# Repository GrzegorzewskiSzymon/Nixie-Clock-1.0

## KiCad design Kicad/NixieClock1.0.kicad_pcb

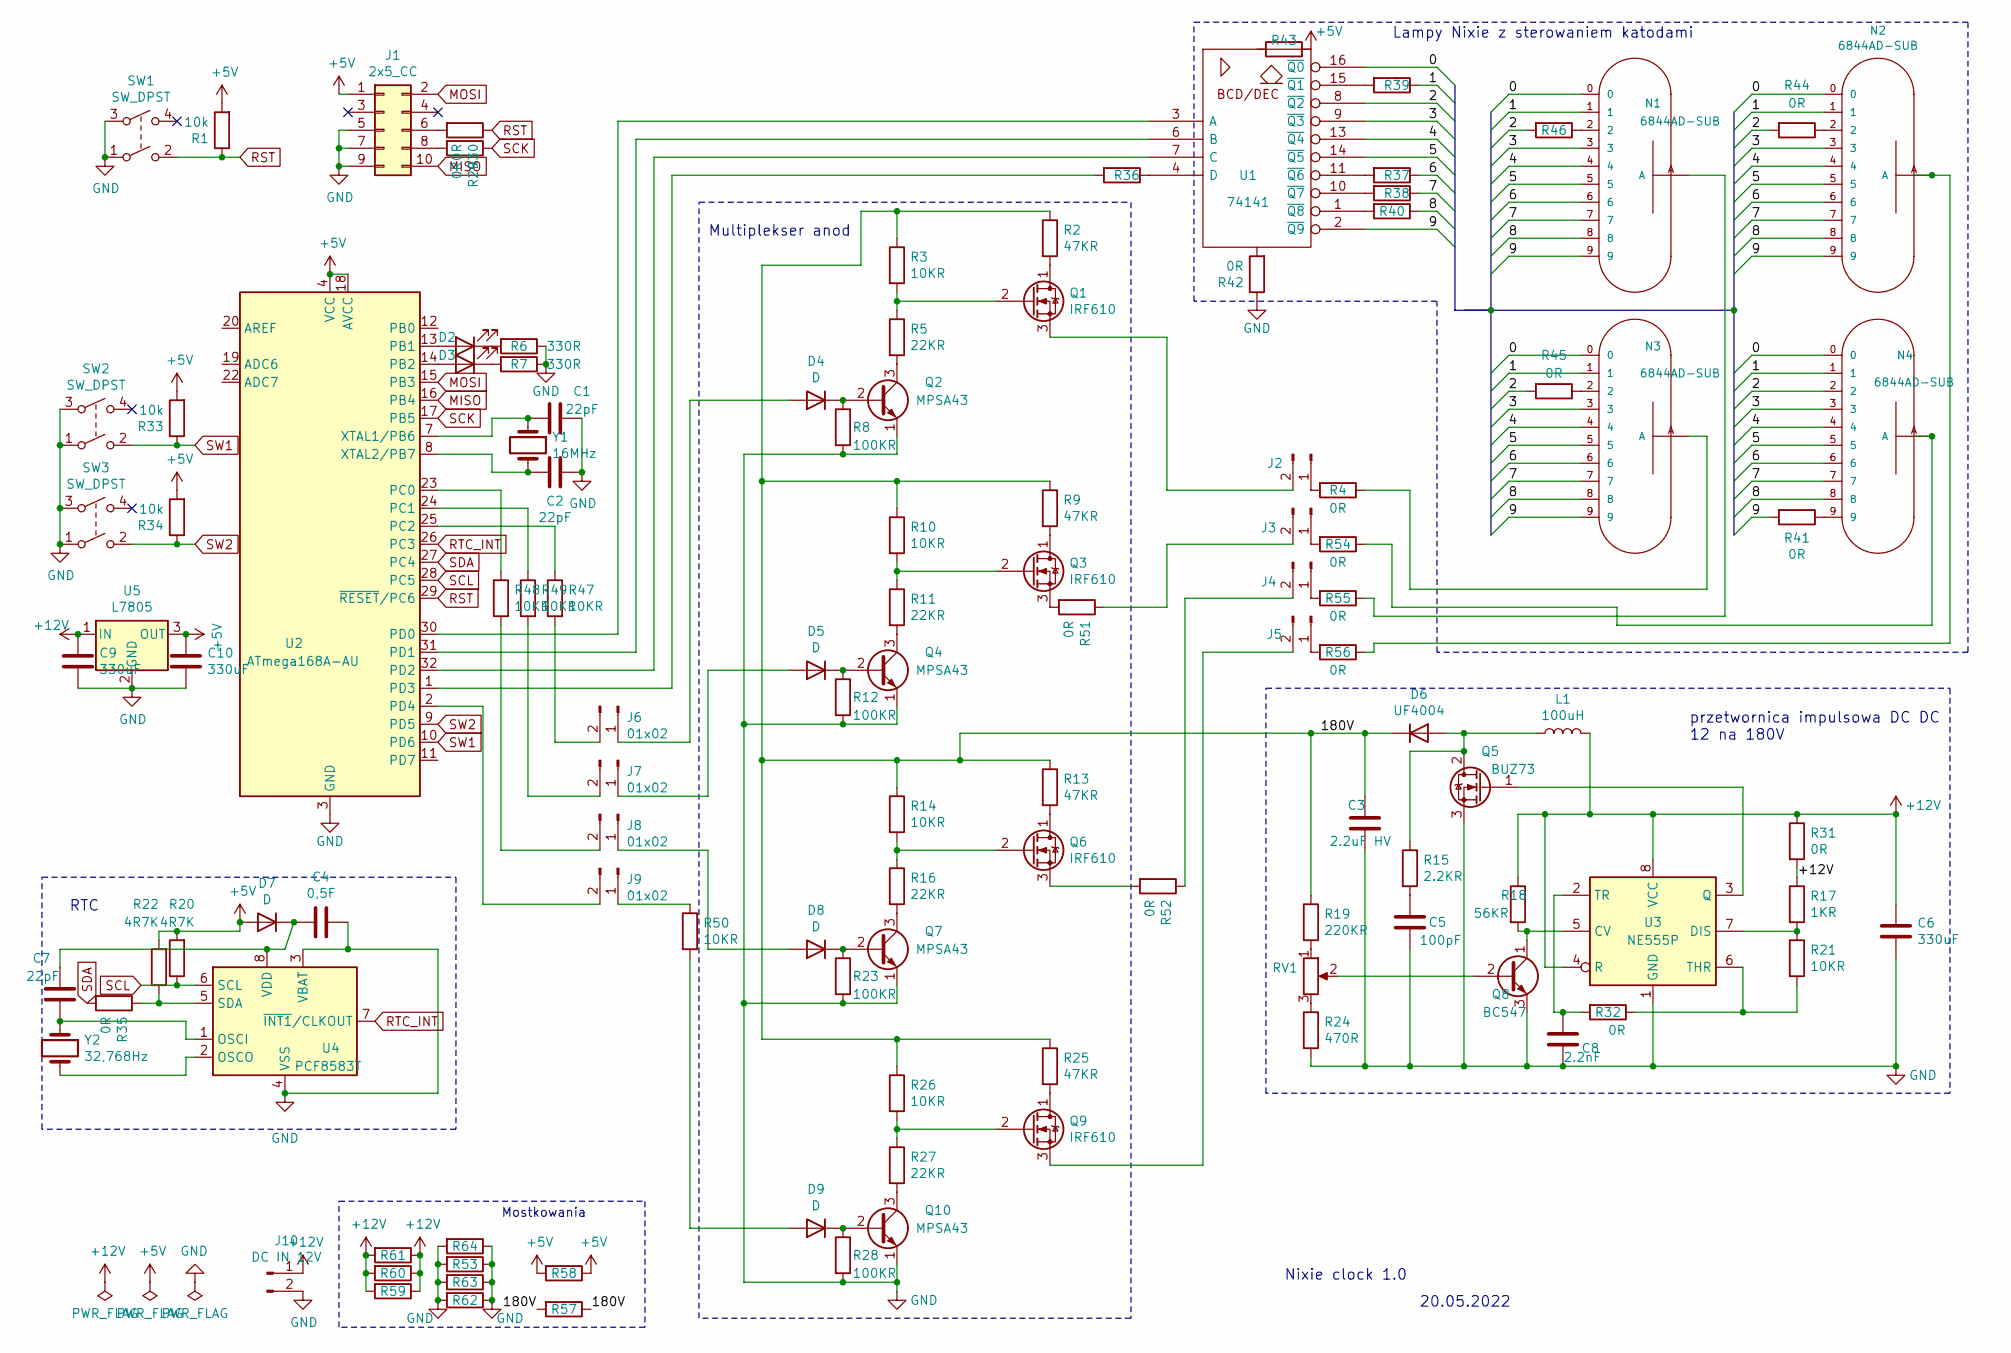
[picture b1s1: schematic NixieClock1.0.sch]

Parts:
C1, C2, C7: 22pF; C_Disc_D3.0mm_W2.0mm_P2.50mm
C3: 2.2uF HV; CP_Radial_D5.0mm_P2.50mm
C4: 0,5F; CP_Radial_D6.3mm_P2.50mm
C5: 100pF; C_Disc_D5.0mm_W2.5mm_P5.00mm
C6, C9, C10: 330uF; CP_Radial_D5.0mm_P2.50mm
C8: 2.2nF; C_Disc_D3.0mm_W2.0mm_P2.50mm
D2, D3: LED; LED_1206_3216Metric_Pad1.42x1.75mm_HandSolder
D4, D5, D7, D8, D9: D; D_DO-34_SOD68_P7.62mm_Horizontal
D6: UF4004; D_DO-34_SOD68_P7.62mm_Horizontal
J1: 2x5_CC; PinSocket_2x05_P2.54mm_Vertical
J2, J3, J4, J5, J6, J7, J8, J9: 01x02; PinHeader_1x02_P2.54mm_Vertical
J10: DC IN 12V; BarrelJack_CUI_PJ-102AH_Horizontal
L1: 100uH; L_Axial_L6.6mm_D2.7mm_P2.54mm_Vertical_Vishay_IM-2
N1, N2, N3, N4: 6844AD-SUB; Z5740m
Q1, Q3, Q6, Q9: IRF610; TO-220-3_Vertical
Q2, Q4, Q7, Q10: MPSA43; TO-92_Inline
Q5: BUZ73; TO-220-3_Vertical
Q8: BC547; TO-92_Inline
R1, R33, R34: 10k; R_1206_3216Metric_Pad1.30x1.75mm_HandSolder
R2, R9, R13, R25: 47KR; R_Axial_DIN0207_L6.3mm_D2.5mm_P7.62mm_Horizontal
R3, R10, R14, R21, R26, R50: 10KR; R_1206_3216Metric_Pad1.30x1.75mm_HandSolder
R4, R30, R31, R32, R36, R37, R38, R42, R43, R54, R55, R56, R57, R58, R59, R64: 0R; R_Axial_DIN0207_L6.3mm_D2.5mm_P7.62mm_Horizontal
R5, R11, R16, R27: 22KR; R_Axial_DIN0207_L6.3mm_D2.5mm_P7.62mm_Horizontal
R6, R7: 330R; R_1206_3216Metric_Pad1.30x1.75mm_HandSolder
R8, R12, R23, R28: 100KR; R_Axial_DIN0207_L6.3mm_D2.5mm_P7.62mm_Horizontal
R15: 2.2KR; R_Axial_DIN0207_L6.3mm_D2.5mm_P7.62mm_Horizontal
R17: 1KR; R_Axial_DIN0207_L6.3mm_D2.5mm_P7.62mm_Horizontal
R18: 56KR; R_Axial_DIN0207_L6.3mm_D2.5mm_P7.62mm_Horizontal
R19: 220KR; R_Axial_DIN0207_L6.3mm_D2.5mm_P7.62mm_Horizontal
R20, R22: 4R7K; R_Axial_DIN0207_L6.3mm_D2.5mm_P7.62mm_Horizontal
R24: 470R; R_Axial_DIN0207_L6.3mm_D2.5mm_P7.62mm_Horizontal
R29, R35, R40, R41, R44, R45, R46, R51, R52, R53, R60, R61, R62, R63: 0R; R_1206_3216Metric_Pad1.30x1.75mm_HandSolder
R39: e; R_1206_3216Metric_Pad1.30x1.75mm_HandSolder
R47, R48, R49: 10KR; R_Axial_DIN0207_L6.3mm_D2.5mm_P7.62mm_Horizontal
RV1: R_POT 1K; Potentiometer_ACP_CA9-H2,5_Horizontal
SW1, SW2, SW3: SW_DPST; SW_PUSH_6mm_H4.3mm
U1: 74141; DIP-16_W7.62mm_Socket_LongPads
U2: ATmega168A-AU; TQFP-32_7x7mm_P0.8mm
U3: NE555P; DIP-8_W7.62mm
U4: PCF8583T; SOIC-8_3.9x4.9mm_P1.27mm
U5: L7805; DPAK-3
Y1: 16MHz; Resonator-2Pin_W10.0mm_H5.0mm
Y2: 32,768Hz; Crystal_DS15_D1.5mm_L5.0mm_Vertical

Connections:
+5V: C10.1, D7.2 (A), J1.1, R1.2, R20.2, R22.2, R33.2, R34.2, R43.2, R58.1, R58.2, U2.4 (VCC), U2.6 (VCC), U2.18 (AVCC), U5.3 (OUT)
+12V: C6.1, C9.1, J10.1, L1.2, R17.1, R18.1, R31.1, R31.2, R59.1, R59.2, R60.1, R60.2, R61.1, R61.2, U3.4 (R), U3.8 (VCC), U5.1 (IN)
/0: N1.0, N2.0, N3.0, N4.0, U1.16 (~Q0)
/1: N1.1, N2.1, N3.1, N4.1, R39.1
/2: N4.2, R44.2, R45.2, R46.2, U1.8 (~Q2)
/3: N1.3, N2.3, N3.3, N4.3, U1.9 (~Q3)
/4: N1.4, N2.4, N3.4, N4.4, U1.13 (~Q4)
/5: N1.5, N2.5, N3.5, N4.5, U1.14 (~Q5)
/6: N1.6, N2.6, N3.6, N4.6, R37.1
/7: N1.7, N2.7, N3.7, N4.7, R38.1
/8: N1.8, N2.8, N3.8, N4.8, R40.1
/9: N1.9, N2.9, N3.9, R41.2, U1.2 (~Q9)
/180V: C3.1, D6.1 (K), R2.1, R3.1, R9.1, R10.1, R13.1, R14.1, R19.1, R25.1, R26.1, R57.1, R57.2
MISO: J1.10, U2.16 (PB4)
MOSI: J1.2, U2.15 (PB3)
unnamed: C1.2, U2.7 (XTAL1/PB6), Y1.1
unnamed: C2.2, U2.8 (XTAL2/PB7), Y1.2
unnamed: C5.1, R15.2
unnamed: C7.1, U4.1 (OSCI), Y2.1
unnamed: C8.1, R32.2, U3.2 (TR)
unnamed: D2.1 (K), R6.2
unnamed: D2.2 (A), U2.13 (PB1)
unnamed: D3.1 (K), R7.2
unnamed: D3.2 (A), U2.14 (PB2)
unnamed: D4.1 (K), Q2.2 (B), R8.1
unnamed: D4.2 (A), J6.1
unnamed: D5.1 (K), Q4.2 (B), R12.1
unnamed: D5.2 (A), J7.1
unnamed: D6.2 (A), L1.1, Q5.2 (D), R15.1
unnamed: D8.1 (K), Q7.2 (B), R23.1
unnamed: D8.2 (A), J8.1
unnamed: D9.1 (K), Q10.2 (B), R28.1
unnamed: D9.2 (A), R50.2
unnamed: J1.6, R30.2
unnamed: J1.8, R29.2
unnamed: J2.1, R4.2
unnamed: J2.2, Q1.3 (S)
unnamed: J3.1, R54.2
unnamed: J3.2, R51.1
unnamed: J4.1, R55.2
unnamed: J4.2, R52.1
unnamed: J5.1, R56.2
unnamed: J5.2, Q9.3 (S)
unnamed: J6.2, R47.2
unnamed: J7.2, R49.2
unnamed: J8.2, R48.2
unnamed: J9.1, R50.1
unnamed: J9.2, U2.2 (PD4)
unnamed: N1.2, R46.1
unnamed: N1.A, R55.1
unnamed: N2.2, R44.1
unnamed: N2.A, R56.1
unnamed: N3.2, R45.1
unnamed: N3.A, R4.1
unnamed: N4.9, R41.1
unnamed: N4.A, R54.1
unnamed: Q1.1 (D), R2.2
unnamed: Q1.2 (G), R3.2, R5.1
unnamed: Q2.3 (C), R5.2
unnamed: Q3.1 (D), R9.2
unnamed: Q3.2 (G), R10.2, R11.1
unnamed: Q3.3 (S), R51.2
unnamed: Q4.3 (C), R11.2
unnamed: Q5.1 (G), U3.3 (Q)
unnamed: Q6.1 (D), R13.2
unnamed: Q6.2 (G), R14.2, R16.1
unnamed: Q6.3 (S), R52.2
unnamed: Q7.3 (C), R16.2
unnamed: Q8.1 (C), R18.2, U3.5 (CV)
unnamed: Q8.2 (B), RV1.2
unnamed: Q9.1 (D), R25.2
unnamed: Q9.2 (G), R26.2, R27.1
unnamed: Q10.3 (C), R27.2
unnamed: R17.2, R21.1, U3.7 (DIS)
unnamed: R19.2, RV1.1
unnamed: R21.2, R32.1, U3.6 (THR)
unnamed: R22.1, R35.1, U4.5 (SDA)
unnamed: R24.1, RV1.3
unnamed: R36.1, U1.4 (D)
unnamed: R36.2, U2.1 (PD3)
unnamed: R37.2, U1.11 (~Q6)
unnamed: R38.2, U1.10 (~Q7)
unnamed: R39.2, U1.15 (~Q1)
unnamed: R40.2, U1.1 (~Q8)
unnamed: R47.1, U2.25 (PC2)
unnamed: R48.1, U2.23 (PC0)
unnamed: R49.1, U2.24 (PC1)
unnamed: U1.3 (A), U2.30 (PD0)
unnamed: U1.6 (B), U2.31 (PD1)
unnamed: U1.7 (C), U2.32 (PD2)
unnamed: U4.2 (OSCO), Y2.2
RST: R1.1, R30.1, SW1.2, U2.29 (~RESET~/PC6)
RTC_INT: U2.26 (PC3), U4.7 (~INT1~/CLKOUT)
SCK: R29.1, U2.17 (PB5)
SCL: R20.1, U2.28 (PC5), U4.6 (SCL)
SDA: R35.2, U2.27 (PC4)
SW1: R33.1, SW2.2, U2.10 (PD6)
SW2: R34.1, SW3.2, U2.9 (PD5)
VCC: R43.1, U1.5 (VCC)

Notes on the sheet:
przetwornica impulsowa DC DC 12 na 180V
Lampy Nixie z sterowaniem katodami
Multiplekser anod
RTC
Mostkowania
Nixie clock 1.0
20.05.2022

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
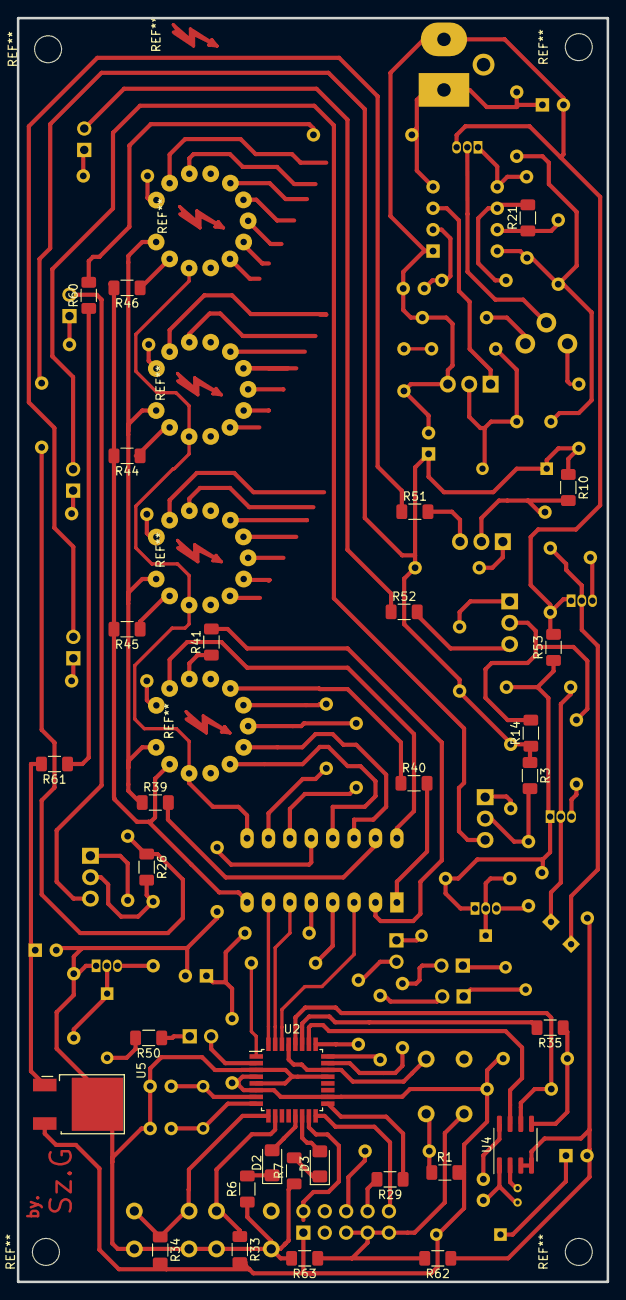
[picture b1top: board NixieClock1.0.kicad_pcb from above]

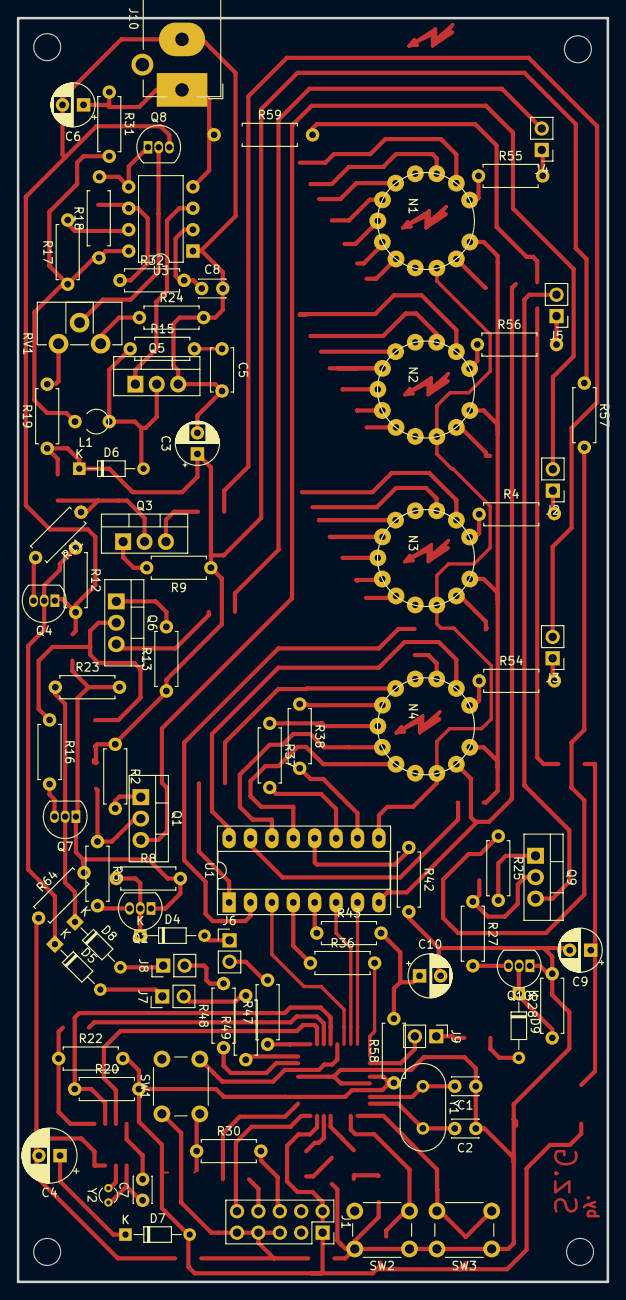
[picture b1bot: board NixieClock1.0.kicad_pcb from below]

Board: 2 copper layers, 70.0 x 150.0 mm, 118 parts (87 on the bottom side), 102 nets.

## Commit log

2022-05-26 add .gitignore
2022-05-28 feat: change i2c to hardware implementation
    refactor: move parts of code from main to Libraries/RTC/ and Libraries/Utils/
2022-05-29 add simple implementations for driving nixie tubes in Libraries/NixieDrivers/
2022-05-29 add interrupt implementation to measure runtime since start in milliseconds
2022-05-29 add function "DisplayTime(hours, minutes)" to display hours and minutes but it overwrite whole PORTD which could lead to problems witch buttons in future
2022-06-01 add non blocking functions to count number of presses on buttons, along with fast counting after pressing button for over 2,5sec (can be easily change in utils.h) this implemantation require timer 0 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
2022-06-01 change RTC init function "RtcInit()" in "Libraries/RTC/pcf8583.c" to change time by simply pressing buttons which lead to minor not important changes in SN74141.x
2022-06-04 correct bug when decreasing from 00:00 [hh:mm] and also RTC is not overwritten with every reset in Libraries/RTC/pcf8583.c
    adjust timing in Libraries/Utils/utils.h
2022-06-04 add slow multiplexing for 30 seconds every 5 min to longen life of nixie tubes
2022-06-05 add schematics
